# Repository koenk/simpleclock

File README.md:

# SimpleClock

A small USB powered clock with 7-segment display.

This clock is designed to be minimal, only capable of showing the current time.
The PCB with all components is the same size as the 4x7-segment display itself,
making the fully assembled clock as big as a 4x7-segment display with its pins.

The clock has a micro-usb connector for power, a header for programming the
(AVR) microcontroller, and a header for serial I/O. The clock has no buttons or
other physical inputs; the time is programmed using the serial I/O with
a computer. The brightness of the display can also be configured this way.

A battery-backed RTC keep track of time even when the clock is not plugged into
a 5V power source. The display and MCU are only powered when a 5V source is
connected (normally, via the micro-usb port).

The `pcb` folder contains KiCad files for the schema and PCB design. The `src`
folder contains the code for the microcontroller, which can be built and flashed
using `make install` in the `src` directory. The `control.py` script
communicates with the clock over a serial connection; see `control.py -h` for
all available operations.

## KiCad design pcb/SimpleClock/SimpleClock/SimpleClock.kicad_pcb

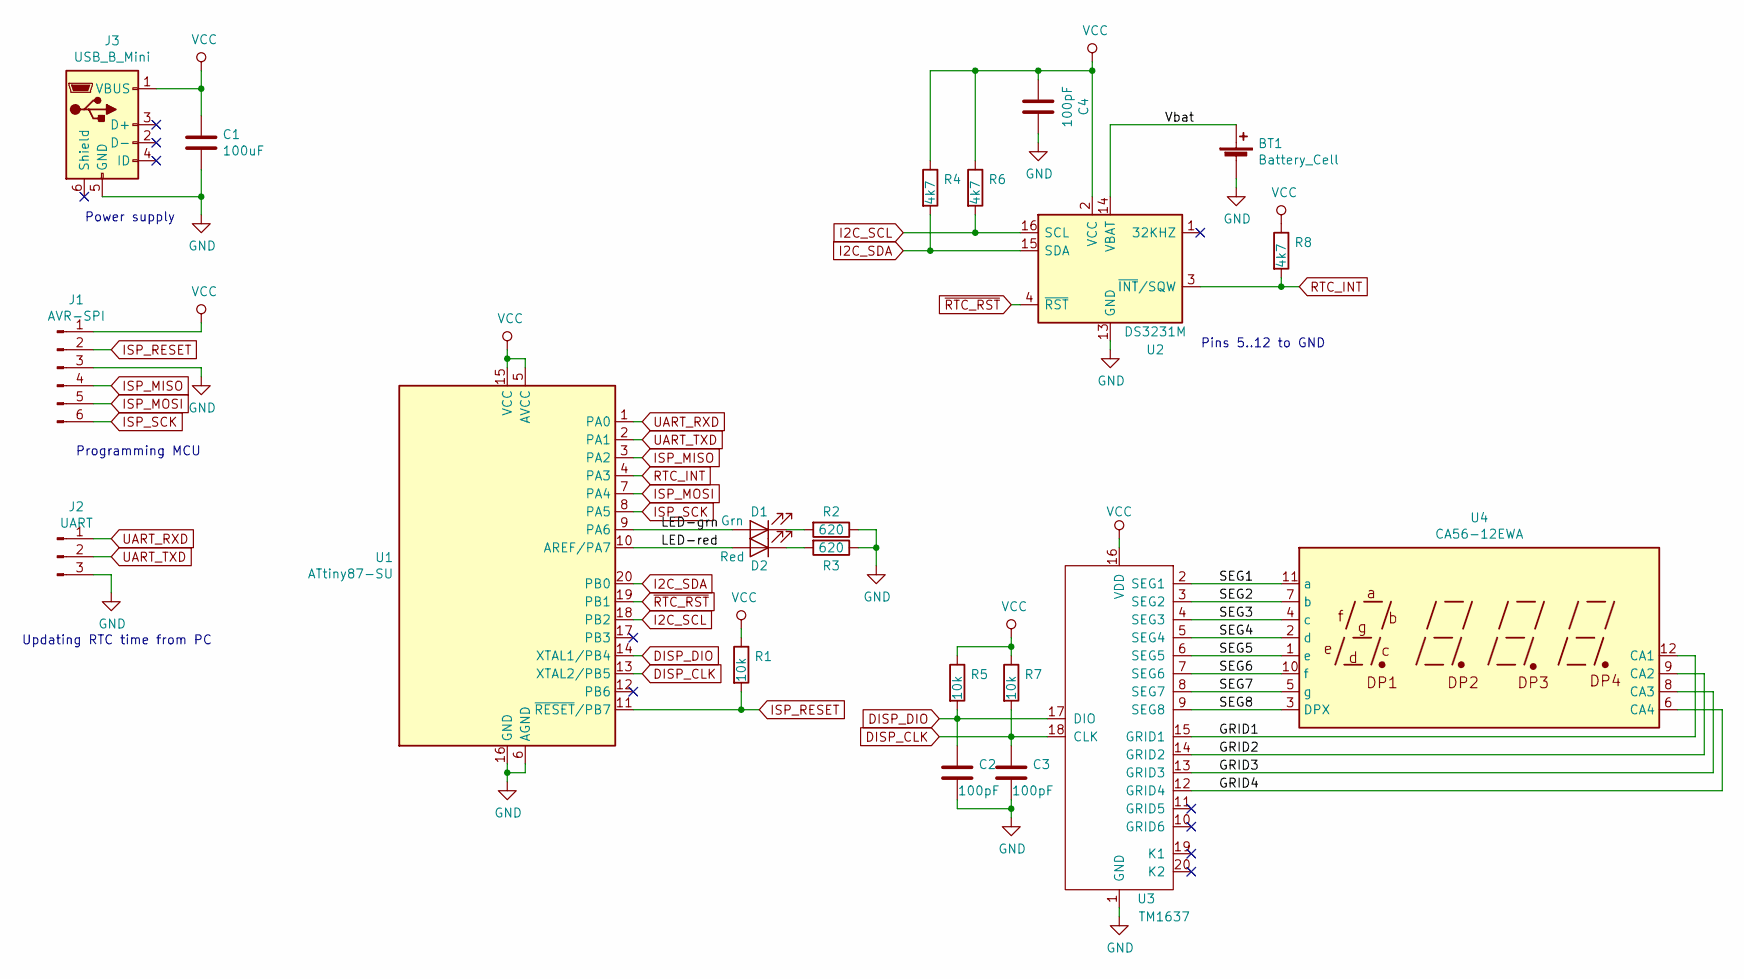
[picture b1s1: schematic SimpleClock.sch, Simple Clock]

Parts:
BT1: Battery_Cell; BatteryHolder_Keystone_3000_1x12mm
C1: 100uF; C_0805_2012Metric_Pad1.15x1.40mm_HandSolder
C2, C3, C4: 100pF; C_0805_2012Metric_Pad1.15x1.40mm_HandSolder
D1: Grn; LED_0603_1608Metric_Pad1.05x0.95mm_HandSolder
D2: Red; LED_0603_1608Metric_Pad1.05x0.95mm_HandSolder
J1: AVR-SPI; PinHeader_2x03_P2.54mm_Vertical
J2: UART; PinHeader_1x03_P2.54mm_Vertical
J3: USB_B_Mini; USB_Micro-B_4DIP
R1, R5, R7: 10k; R_0805_2012Metric_Pad1.15x1.40mm_HandSolder
R2, R3: 620; R_0805_2012Metric_Pad1.15x1.40mm_HandSolder
R4, R6, R8: 4k7; R_0805_2012Metric_Pad1.15x1.40mm_HandSolder
U1: ATtiny87-SU; SOIC-20W_7.5x12.8mm_P1.27mm
U2: DS3231M; SOIC-16W_7.5x10.3mm_P1.27mm
U3: TM1637; SOIC-20W_7.5x12.8mm_P1.27mm
U4: CA56-12EWA

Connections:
/GRID1: U3.15 (GRID1), U4.12 (CA1)
/GRID2: U3.14 (GRID2), U4.9 (CA2)
/GRID3: U3.13 (GRID3), U4.8 (CA3)
/GRID4: U3.12 (GRID4), U4.6 (CA4)
/LED-grn: D1.2 (A), U1.9 (PA6)
/LED-red: D2.2 (A), U1.10 (AREF/PA7)
/SEG1: U3.2 (SEG1), U4.11 (a)
/SEG2: U3.3 (SEG2), U4.7 (b)
/SEG3: U3.4 (SEG3), U4.4 (c)
/SEG4: U3.5 (SEG4), U4.2 (d)
/SEG5: U3.6 (SEG5), U4.1 (e)
/SEG6: U3.7 (SEG6), U4.10 (f)
/SEG7: U3.8 (SEG7), U4.5 (g)
/SEG8: U3.9 (SEG8), U4.3 (DPX)
/Vbat: BT1.1 (+), U2.14 (VBAT)
DISP_CLK: C3.1, R7.2, U1.13 (XTAL2/PB5), U3.18 (CLK)
DISP_DIO: C2.1, R5.2, U1.14 (XTAL1/PB4), U3.17 (DIO)
GND: BT1.2 (-), C1.2, C2.2, C3.2, C4.1, J1.3, J2.3, J3.5 (GND), R2.1, R3.1, U1.6 (AGND), U1.16 (GND), U2.5 (GND), U2.6 (GND), U2.7 (GND), U2.8 (GND), U2.9 (GND), U2.10 (GND), U2.11 (GND), U2.12 (GND), U2.13 (GND), U3.1 (GND)
I2C_SCL: R6.2, U1.18 (PB2), U2.16 (SCL)
I2C_SDA: R4.2, U1.20 (PB0), U2.15 (SDA)
ISP_MISO: J1.4, U1.3 (PA2)
ISP_MOSI: J1.5, U1.7 (PA4)
ISP_RESET: J1.2, R1.2, U1.11 (~RESET~/PB7)
ISP_SCK: J1.6, U1.8 (PA5)
unnamed: D1.1 (K), R2.2
unnamed: D2.1 (K), R3.2
RTC_INT: R8.2, U1.4 (PA3), U2.3 (~INT~/SQW)
UART_RXD: J2.1, U1.1 (PA0)
UART_TXD: J2.2, U1.2 (PA1)
VCC: C1.1, C4.2, J1.1, J3.1 (VBUS), R1.1, R4.1, R5.1, R6.1, R7.1, R8.1, U1.5 (AVCC), U1.15 (VCC), U2.2 (VCC), U3.16 (VDD)
~RTC_RST: U1.19 (PB1), U2.4 (~RST)

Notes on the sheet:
Pins 5..12 to GND
Updating RTC time from PC
Programming MCU
Power supply

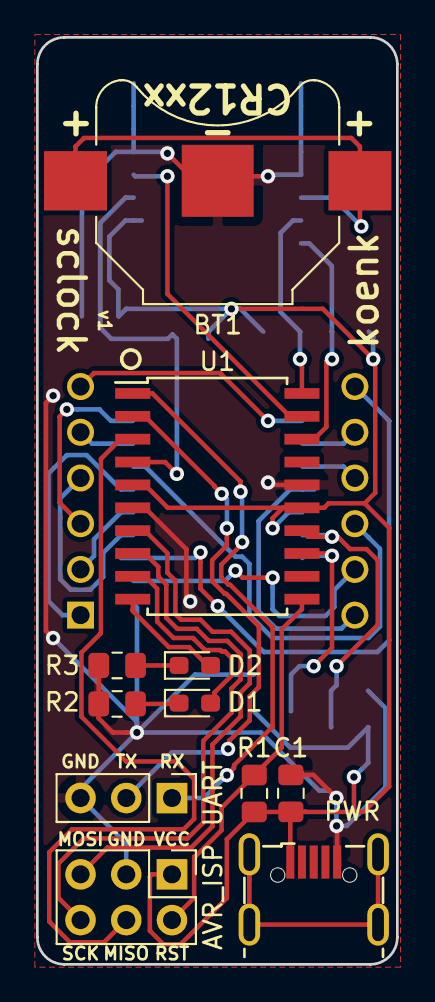
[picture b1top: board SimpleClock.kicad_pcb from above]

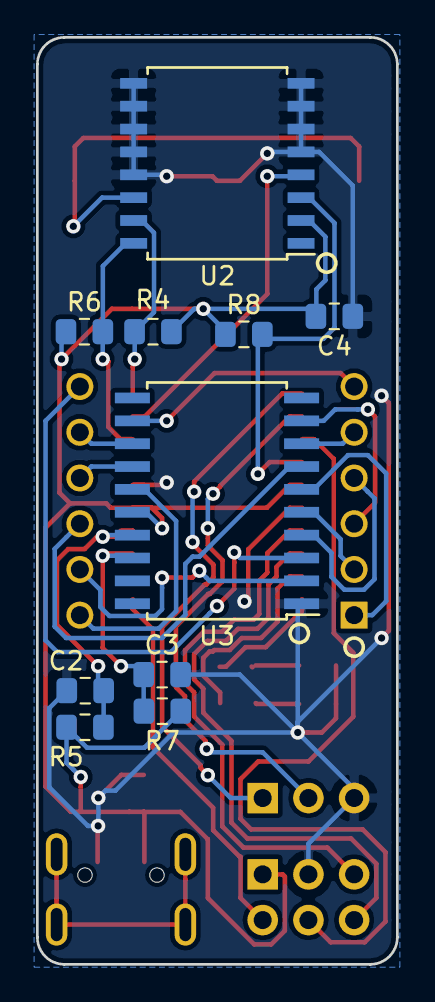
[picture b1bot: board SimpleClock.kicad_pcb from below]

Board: 2 copper layers, 20.0 x 51.5 mm, 22 parts (11 on the bottom side), 31 nets.

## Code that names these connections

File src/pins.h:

/*
 * Abstraction layer for I/O of AVR ports.
 */

#ifndef PINS_H
#define PINS_H

#include <stdlib.h>

#include <avr/io.h>

#include "types.h"

/* Pin mappings, pins go from 1 to 20 */
#define PIN_UART_RX 1
#define PIN_UART_TX 2

#define PIN_RTC_INT 4 /* INT1 */

#define PIN_LED1 9
#define PIN_LED2 10

#define PIN_ISP_MISO 3
#define PIN_ISP_MOSI 7
#define PIN_ISP_SCK 8
#define PIN_ISP_RST 11

#define PIN_DISP_CLK 13
#define PIN_DISP_DIO 14

#define PIN_TWI_SDA 20
#define PIN_TWI_SCL 18
#define PIN_RTC_RST 19

#define INPUT 0
#define OUTPUT 1

/*
 * Pins that we can do I/O on.
 */
static inline u8 pin_valid(u8 pin)
{
    if (pin == 0 || pin > 20)
        return 0;
    /* VCC/GND and AVCC/AGND */
    if (pin == 5 || pin == 6 || pin == 15 || pin == 16)
        return 0;
    return 1;
}

/*
 * Map a pin (1..20) to the bit number for its registers (e.g., DDRA or PORTB).
 */
static inline u8 pin_to_bit(u8 pin)
{
    if (!pin_valid(pin))
        return 8;
    else if (pin <= 4)
        return pin - 1;
    else if (pin <= 10)
        return pin - 3; /* skip AVCC/AGND */
    else if (pin <= 14)
        return 18 - pin; /* skip VCC/GND */
    else
        return 20 - pin;
}

/*
 * Bitmask for a given pin (1..20) for its corresponding registers.
 */
static inline u8 pin_to_mask(u8 pin)
{
    return 1 << pin_to_bit(pin);
}

static inline volatile u8 *pin_to_control_reg(u8 pin)
{
    if (pin <= 10)
        return &DDRA;
    if (pin <= 20)
        return &DDRB;
    return NULL;
}
static inline volatile u8 *pin_to_output_reg(u8 pin)
{
    if (pin <= 10)
        return &PORTA;
    if (pin <= 20)
        return &PORTB;
    return NULL;
}
static inline volatile u8 *pin_to_input_reg(u8 pin)
{
    if (pin <= 10)
        return &PINA;
    if (pin <= 20)
        return &PINB;
    return NULL;
}

static inline void pin_set_mode(u8 pin, u8 mode)
{
    volatile u8 *reg = pin_to_control_reg(pin);
    u8 mask = pin_to_mask(pin);

    if (!pin_valid(pin))
        return;

    if (mode == INPUT)
        *reg &= ~mask;
    else
        *reg |= mask;
}

static inline void pin_write(u8 pin, u8 val)
{
    volatile u8 *reg = pin_to_output_reg(pin);
    u8 mask = pin_to_mask(pin);

    if (!pin_valid(pin))
        return;

    if (val)
        *reg |= mask;
    else
        *reg &= ~mask;
}

static inline u8 pin_read(u8 pin)
{
    volatile u8 *reg = pin_to_output_reg(pin);
    u8 mask = pin_to_mask(pin);

    if (!pin_valid(pin))
        return 0;

    return (*reg & mask) ? 1 : 0;
}

#endif

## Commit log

2019-02-17 Microcontroller code for first fully functional prototype
2019-02-17 Script to interface with SimpleClock hardware over serial port
2019-02-17 Record git version in microcontroller code
2019-02-17 Brightness configuration
2019-02-18 Sleep MCU
2019-03-02 Fix colon in middle
2019-03-02 Debug blinky led mode (disabled)
2019-03-02 Fix line endings
2019-04-24 Store brightness in eeprom
2019-04-24 Import schematic and PCB design
2019-04-30 README and pictures of the finished clock
2019-04-30 Add MIT license
2019-06-07 Move strings to progmem (ROM)
2020-10-25 Improve date/time code, control protocol and add support for counting to/from dates
